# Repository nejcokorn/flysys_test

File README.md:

# FlySys Hardware Plan

Updated: 2026-06-08

This folder is intentionally a planning workspace only. The next hardware build will be created from scratch in Atopile. Old EasyEDA, KiCad, generated production files, and JLC-specific draft outputs are not part of the active design.

## Goal

Build a compact FlySys variometer board with:

- BLE-first telemetry and configuration.
- Accurate pressure-based vertical-speed sensing.
- 6-axis inertial sensing for filtering/orientation support.
- LiPo charging and battery operation.
- Loud firmware-controlled audio output.
- USB mass-storage device access for logs/configuration.
- Power button, hidden BOOT/RESET recovery controls, green power LED, blue BLE pairing LED, USB, and software-first firmware update access without debug pads.

## Selected Components

| Function | Selection | Supplier note |
| --- | --- | --- |
| MCU/BLE/Wi-Fi/USBMSD | Espressif `ESP32-S3-WROOM-1U-N8` | Use ESP32-S3 because USBMSD needs configurable USB device support. `N8` provides 8 MB flash and has no PSRAM. The `1U` variant uses the module U.FL/I-PEX MHF1 connector for an off-board antenna. |
| External antenna | Pulse `ANTX200P001B24003` | Off-board 2.4 GHz adhesive flat patch antenna for the WROOM-1U U.FL/I-PEX MHF1 connector. It is a DigiKey order item, not a PCB footprint. |
| Pressure sensors | 2 x Bosch `BMP581` | Dual altitude/variometer pressure sensors on the same I2C bus. `U5` uses address `0x46`; `U6` uses address `0x47`. |
| 6-axis IMU | Bosch `BMI323` | Primary accelerometer/gyro. |
| Magnetometer | Not fitted | Keep unpopulated I2C pads or optional footprint for future magnetometer. |
| Charger / power path | TI `BQ24075RGTR` | 1S LiPo charger with power-path management. |
| 3.3 V regulator | TI `TLV75533PDBVR` | Replaces `AP2112K-3.3TRG1` because AP2112 was 0 stock in the DigiKey.si audit. Recheck current and thermal margin with ESP32-S3 peaks. Add local bulk capacitance near the module. |
| USB | GCT `USB4105-GF-A` + ST `USBLC6-2SC6Y` | USB-C 2.0 receptacle and automotive/AEC-Q101 USB ESD for charging, ESP32-S3 native USB, USBMSD, logs, and flashing. |
| Audio | Same Sky `CSS-J4D20-SMT-TR` + `AO3400A` N-MOSFET | Externally driven SMD magnetic transducer from the old device BOM. Drive from the 1S battery/SYS rail; keep firmware tone, carrier-duty, and envelope control. |
| User input | C&K `KMR211NG LFS` | Momentary active-low tactile switch for power/user input plus hidden BOOT and RESET service switches. Final actuator and pinhole geometry still depends on enclosure height. |
| Indicators | Lite-On `LTST-C190GKT` + `LTST-C190TBKT` | 0603 LEDs: green always-on `+3V3` power-present indicator, blue firmware-controlled BLE pairing/advertising indicator. The blue LED is driven from `SYS` with a GPIO-controlled low-side MOSFET. |
| Battery | JST `S2B-PH-SM4-TB` | 2-pin JST-PH right-angle SMD header. Confirm protected pack and cable polarity. |
| Firmware update | Application-level updater + hidden ESP32-S3 BOOT/RESET recovery | Normal users update through firmware while USB or another supported link is connected. Debug pads are not fitted; hidden BOOT+RESET remains the recovery fallback for the ESP32-S3 ROM USB bootloader. |

## DigiKey.si Availability Audit

Initial audit checked: 2026-05-31. Audio and LED changes rechecked: 2026-06-01. Stock changes quickly; recheck before ordering.

| Function | MPN | DigiKey cut-tape part | Observed availability | Status |
| --- | --- | --- | --- | --- |
| MCU/BLE/Wi-Fi/USBMSD | `ESP32-S3-WROOM-1U-N8` | `1965-ESP32-S3-WROOM-1U-N8CT-ND` | Recheck before ordering | Selected external-antenna module |
| External antenna | `ANTX200P001B24003` | `311-1553-ND` | Recheck before ordering | Off-board U.FL/I-PEX MHF1 adhesive 2.4 GHz antenna |
| Pressure sensors | `BMP581` | `828-BMP581CT-ND` | Recheck before ordering | Qty 2 selected |
| 6-axis IMU | `BMI323` | `828-BMI323CT-ND` | 663 in stock | Selected |
| Charger / power path | `BQ24075RGTR` | `296-38874-1-ND` | 3,702 in stock | Selected |
| 3.3 V LDO | `TLV75533PDBVR` | `296-50411-1-ND` | 110,688 in stock | Selected |
| USB-C receptacle | `USB4105-GF-A` | `2073-USB4105-GF-ACT-ND` | 126,702 in stock | Selected |
| USB ESD | `USBLC6-2SC6Y` | `497-11882-1-ND` | 35,783 in stock | Selected automotive/AEC-Q101 part; LCSC `C2969755` |
| Battery connector | `S2B-PH-SM4-TB` | `455-S2B-PH-SM4-TBCT-ND` | 71,350 in stock | Selected |
| Loud SMD buzzer | `CSS-J4D20-SMT-TR` | `102-1198-1-ND` | 2,332 in stock | Selected old-device buzzer: externally driven magnetic transducer, 90 dB at 3.6 V, 5 cm, 80 mA, 3.1 kHz |
| N-MOSFETs | `AO3400A` | `785-1000-1-ND` | 168,023 in stock | Low-side drivers for buzzer PWM, blue BLE pairing LED switching, and power-latch control |
| Battery switch P-MOSFET | `DMP3098L-7` | `DMP3098LDICT-ND` | Recheck before ordering | High-side hard-off switch between battery connector and internal `BAT` rail |
| Power-start diodes | `1N4148W-7-F` | `1N4148W-FDICT-ND` | Recheck before ordering | Diode isolation for power button, battery switch gate, and charger `SYSOFF` |
| User button | `KMR211NG LFS` | `CKN10243CT-ND` | 44,917 in stock | Selected |
| Power LED | `LTST-C190GKT` | `160-LTST-C190GKTCT-ND` | 1,068,260 in stock | Selected 0603 green LED, 2.1 V typical Vf |
| BLE LED | `LTST-C190TBKT` | `160-1646-1-ND` | 92,246 in stock | Selected 0603 blue LED for BLE pairing/advertising indication, 3.3 V typical Vf |
| Resistors | Yageo `RC0603FR` 1% 0603 family | Value-specific | `RC0603FR-0710KL` observed at 9,468,329 in stock | Use same family for 100R, 1k, 3k, 5.1k, 10k, 100k, 1M as needed |
| 100 nF decoupling capacitor | Samsung `CL10B104KB8NNNC` | `1276-1000-1-ND` | 9,953,497 in stock | Selected family |
| Other ceramics | Samsung CL-series MLCCs | Value-specific | Not individually locked yet | Select exact 1 uF, 10 uF, and 220 nF parts during Atopile binding |

Main audit result: all selected active semiconductors, sensors, connector choices, audio parts, button, LED, and common passives are available from DigiKey.si.

## Baseline Electrical Architecture

- `USB_VBUS`: USB-C 5 V input to charger and USB VBUS sense divider/comparator.
- `SYS`: BQ24075 system output.
- `BAT_RAW`: protected 1S LiPo positive terminal at the connector.
- `BAT`: switched internal battery rail after the hard-off P-MOSFET.
- `+3V3`: TLV75533 output powering ESP32-S3, both BMP581 sensors, BMI323, and optional magnetometer pads.
- `I2C_SCL`, `I2C_SDA`: shared sensor bus for BMP581 `U5`, BMP581 `U6`, BMI323, and DNP magnetometer option.
- `USB_OTG_DP`, `USB_OTG_DM`: USB full-speed pair to ESP32-S3 native USB pins (`GPIO20` D+, `GPIO19` D-).
- `BUZZER_VM`: battery/SYS-powered audio rail feeding the buzzer; no boost in the baseline.
- `BUZZER_PWM`: ESP32-S3 PWM-capable GPIO to the MOSFET gate.
- `PWR_SW_N`: raw active-low power switch node.
- `PWR_BTN_N`: diode-isolated active-low button input to ESP32-S3.
- `BOOT_USER_BTN_N`: ESP32-S3 GPIO0 boot strap, pulled low by the hidden BOOT service button for ROM bootloader recovery.
- `BAT_SENSE`: high-value divider from switched `BAT` to ESP32-S3 ADC-capable GPIO; it has no DC path to `BAT_RAW` when the hard-off switch is open.
- `POWER_LED`: low-current green `+3V3` rail indicator with series resistor. It is on whenever `+3V3` is up and is not firmware-controlled.
- `BLE_LED`: low-current blue indicator for BLE pairing/advertising mode only. Firmware should drive `BLE_LED_PWM` active only while connectable BLE advertising/pairing is active and keep it low or high-Z otherwise. Because the blue LED has high forward voltage, prefer `SYS` plus a current-limit resistor and a small GPIO-controlled low-side switch instead of direct `+3V3` GPIO drive.
- `EN`, `BOOT`: hidden physical RESET and BOOT service controls for ESP32-S3 ROM bootloader recovery only.

## USBMSD / Storage Plan

USBMSD is now a baseline requirement. Use ESP32-S3 native USB OTG device mode with the ESP-IDF TinyUSB MSC class.

Route the USB-C D+/D- pair to ESP32-S3 `GPIO20`/`GPIO19`, keep the ESD part near the connector, and add a USB VBUS monitor path because this is a battery-powered, self-powered USB device.

Initial storage options:

- Internal flash FAT partition for small configuration import/export and short log files.
- External SPI flash, SPI NAND, or microSD if host-visible logs need materially more capacity or write endurance.

Do not let firmware and the USB host write the same mounted filesystem at the same time. Define a mode switch or mount arbitration before implementing firmware.

## Firmware Update UX

Normal firmware update is software-first. When USB is connected, application
firmware should expose an update path such as USB MSC drag-and-drop firmware
copy, a USB CDC update tool, BLE DFU, or OTA. The image must be validated before
activation, and firmware should use OTA partitions with rollback so a failed
image can revert automatically.

USB attach is allowed to power the ESP32-S3 electrically. If `USB_VBUS_SENSE`
shows USB present and the user has not pressed `POWER`, firmware enters
USB-attached idle mode instead of starting the vario application. In this mode,
do not start vario sensing, BLE advertising, buzzer output, logging, or normal
flight behavior. Only minimal charging/status indication, the firmware update
endpoint, and an optional command to start normal mode should run.

Pressing `POWER` while USB is connected records user intent and starts the normal
application. The hidden `BOOT` (`GPIO0`) and `RST` (`EN`) controls remain behind
service access only. Recovery sequence: connect USB-C, hold hidden `BOOT`, press
and release hidden `RST`, release `BOOT`, then flash with the ESP32-S3 native USB
ROM bootloader tool.

## Audio Plan

The buzzer must be loud enough for a paragliding vario used in open air with wind noise. Treat acoustic output as a primary requirement, not a secondary indicator.

Use an externally driven passive SMD transducer so firmware keeps control over pitch, cadence, envelope, mute profiles, and sink/climb tone patterns. Do not use an internally driven active buzzer.

Selected audio path:

- Transducer: `CSS-J4D20-SMT-TR`, externally driven magnetic SMD transducer from the old device BOM, 90 dB at 3.6 V, 5 cm, 3.1 kHz, about 80 mA at rated drive.
- Driver: `AO3400A` low-side N-MOSFET, with the buzzer powered from the 1S battery/SYS rail and the MOSFET gate driven by one ESP32-S3 PWM GPIO.

This matches the old `MX270_MiniUP` firmware model: one output-compare PWM channel generated the audio carrier, `beep->volume` changed the carrier duty, and the vario queue changed the beep envelope/cadence. Port that control model to ESP32-S3 LEDC or MCPWM.

Use the battery/SYS rail, not raw USB VBUS. A normal 1S Li-ion/LiPo pack is 4.2 V full and about 3.6-3.7 V nominal; that fits the buzzer's 3-5 V operating range. Confirm BQ24075 `SYS` behavior so the buzzer never sees an out-of-range USB-derived rail.

Drive the buzzer near its 3.1 kHz rated frequency for maximum SPL. For lower volume, prefer carrier-duty control and audible envelope control; avoid detuning far from resonance just to reduce volume. The old firmware's tone table can be reused as a behavioral reference, but final tones should be revalidated against this buzzer in the enclosure.

Add a gate resistor, gate pulldown, local bulk capacitance near the buzzer supply, and a footprint option for coil clamp/snubber parts. Keep the buzzer current loop compact and scope the first PCB for ringing and EMI while the buzzer is running.

The enclosure must include a real acoustic outlet or sound channel. Verify SPL after the PCB is installed in the actual enclosure, because the port, chamber volume, venting, clothing, helmet, and mounting orientation can dominate the result.

## Sensor Plan

Use two BMP581 barometers and one BMI323 as the fitted sensor stack.

`U5` straps `SDO` to `GND` for BMP581 I2C address `0x46`; `U6` straps `SDO` to `+3V3` for address `0x47`. Both sensors strap `CSB` high for I2C mode and have separate interrupt nets, `BMP581_1_INT` and `BMP581_2_INT`.

Do not fit a magnetometer for the first Atopile board. The core variometer behavior depends on pressure and vertical-motion filtering, not absolute compass heading. Without a magnetometer, yaw/heading can drift; that is acceptable for this baseline.

Keep an unpopulated future magnetometer option with:

- `+3V3`
- `GND`
- `I2C_SCL`
- `I2C_SDA`
- Optional `MAG_INT`

Place the optional magnetometer pads away from USB shield, charger, buzzer, battery current loops, steel screws, and magnets.

## Layout Constraints

- Put the ESP32-S3-WROOM-1U-N8 so its U.FL/I-PEX MHF1 connector is accessible for the off-board antenna cable. Provide coax strain relief and keep the antenna away from battery metal, buzzer metal, enclosure metal, and the user's body as much as the enclosure allows.
- Put both BMP581 sensors near the pressure vent and away from heat, board flex, adhesive, conformal coating, and direct buzzer airflow.
- Put BMI323 near the board center in a mechanically stable area and document axis orientation.
- Keep sensor supply decoupling close to each VDD/VDDIO pin.
- Keep USB D+/D- short, impedance-conscious, protected by ESD near the connector, and routed to ESP32-S3 `GPIO20`/`GPIO19`.
- Include USB VBUS monitoring suitable for self-powered USB device behavior.
- Give the buzzer a clear acoustic outlet; do not bury the port in a sealed or foam-covered enclosure pocket.
- Keep buzzer switching current and charger return currents away from sensor ground return.
- Avoid assigning functional loads to ESP32-S3 boot strapping pins, USB pins, and flash/PSRAM-reserved pins until boot behavior and the exact module variant are checked.

## Firmware Impact

- Port board support from Arduino Nano 33 BLE Sense Rev2 / nRF52840 assumptions to ESP32-S3.
- Use ESP32-S3 BLE stack and keep transmission duty cycle low in production.
- Add USBMSD using ESP-IDF TinyUSB MSC over ESP32-S3 native USB OTG.
- Define the USBMSD storage backend and host-visible filesystem.
- Prevent concurrent writes between firmware logging/config code and the mounted USB host filesystem.
- Decide whether USB presents MSC only, CDC+MSC composite, or a boot/mode-selected function.
- Add software-first firmware update handling with image validation and OTA partition rollback.
- On USB attach from off state, enter USB-attached idle mode until `PWR_BTN_N` is pressed or a supported start command is received.
- In USB-attached idle mode, keep vario sensing, BLE normal operation, buzzer output, and logging inactive.
- Add direct dual-BMP581 driver support for I2C addresses `0x46` and `0x47`, including separate `BMP581_1_INT` and `BMP581_2_INT` handling.
- Add direct BMI323 driver support.
- Remove required magnetometer reads from the baseline firmware path.
- Rework GPIO mapping for ESP32-S3, including `BUZZER_PWM`, `PWR_BTN_N`, `PWR_HOLD`, `BAT_SENSE`, `BLE_LED_PWM`, I2C, USB, `EN`, and `BOOT`.
- Add configurable audio profiles for vario use: climb cadence, sink alarm, mute, startup check, and volume/power-saving modes.
- Port the old single-PWM buzzer model, then retune frequency and volume tables around the `CSS-J4D20-SMT-TR` response on the new PCB.
- Revalidate sensor axis mapping and calibration on the actual PCB.

## Open Decisions

- Protected LiPo pack and cable polarity.
- USBMSD storage backend: internal flash FAT partition vs external flash/NAND/microSD.
- USB device mode policy: MSC only, CDC+MSC composite, boot/mode-selected function, and the exact software update endpoint.
- Final volume-control policy: envelope levels, quiet mode, and startup volume.
- Enclosure acoustic outlet, port orientation, and measured SPL after installation.
- Button actuator/enclosure mechanics.
- Final ESP32-S3 GPIO map after strapping-pin, USB-pin, and reserved-pin review.
- Whether `ESP32-S3-WROOM-1U-N8` without PSRAM is sufficient for the final USBMSD firmware.
- RF/EMC certification path for the selected 4.4 dBi external antenna. Espressif's module certification guidance recommends antennas no higher than the certified antenna gain, so this antenna choice may require additional testing.
- TLV75533 current and thermal margin with ESP32-S3 RF peaks and USB-attached operation.
- Whether charger status pins need LEDs or only test pads.
- Final Atopile package/footprint sources and exact passive values.

## Atopile Build Order

1. Create Atopile project scaffold.
2. Add verified packages for ESP32-S3-WROOM-1U-N8, two BMP581 sensors, BMI323, BQ24075, TLV75533, USB-C, USB ESD, LiPo connector, CSS-J4D20 buzzer, MOSFET driver, button, green power LED, blue BLE pairing LED, passives, and the BOM-only external antenna.
3. Capture power path and 3.3 V rail.
4. Capture ESP32-S3 native USB OTG, USB VBUS sense, `EN`, `BOOT`, and hidden service bootloader buttons.
5. Capture both BMP581 sensors and BMI323 on shared I2C.
6. Add unpopulated magnetometer I2C pads or optional footprint.
7. Add the selected USBMSD storage backend if external storage is selected.
8. Capture loud audio and user I/O.
9. Assign supplier/manufacturer metadata for audit.
10. Run electrical/package checks before PCB routing.

## Atopile Project Status

Atopile is now the active project source in this repo:

- `ato.yaml`: Atopile 0.15.7 project config.
- `main.ato`: FlySysVario schematic source and Atopile `RectangularBoardShape` board outline.
- `parts/`: generated and local part definitions, including local draft footprints for battery, buzzer, MOSFETs, signal diodes, buttons, and optional magnetometer pads.
- `layouts/default/default.kicad_pcb`: Atopile-generated layout artifact used by the Atopile Autolayout panel.
- `docs/components-and-placement.md`: component map, passive explanations, and placement intent.

Current modeled nets include USB-C, USB ESD, BQ24075 power path, P-MOS battery hard-off switch, TLV75533 3.3 V rail, ESP32-S3 native USB, I2C sensor bus, two BMP581 barometers, BMI323, battery connector, switched battery/USB sense dividers, buzzer MOSFET driver, always-on green power LED, blue BLE pairing LED low-side switch, power/user button, hidden BOOT and RESET service buttons, and optional future magnetometer pads. See `docs/firmware-update-ux.md` for the software-first update flow and recovery fallback.

`ato --non-interactive build --standalone main.ato:FlySysVario` completes the
current Atopile source workflow. The default layout build still needs a layout
artifact migration after the WROOM-1U swap; `ato --non-interactive build`
passes electrical verification but fails while loading `layouts/default/default.kicad_pcb`.
The 90 mm x 45 mm board outline is defined in `main.ato` with
`RectangularBoardShape`, so the Atopile Autolayout panel has a board boundary to
place and route against. The remaining warnings are expected for local or
DigiKey-only parts because the current picker support is not covering those
local packages. Before production, verify the local draft footprints for
`ESP32-S3-WROOM-1U-N8`, `S2B-PH-SM4-TB`, `CSS-J4D20-SMT-TR`, `AO3400A`,
`DMP3098L`, `1N4148W`, `KMR211NG LFS`, and optional magnetometer pads against
manufacturer land patterns and enclosure mechanics.

## Source Links

- Atopile project structure: https://docs.atopile.io/atopile-0.14.x/essentials/5-project-structure
- Atopile language reference: https://docs.atopile.io/atopile-0.14.x/essentials/1-the-ato-language
- ESP32-S3-WROOM-1/WROOM-1U datasheet: https://documentation.espressif.com/esp32-s3-wroom-1_wroom-1u_datasheet_en.pdf
- DigiKey.si ESP32-S3-WROOM-1U-N8: https://www.digikey.si/en/products/detail/espressif-systems/ESP32-S3-WROOM-1U-N8/16162635
- DigiKey.si Pulse ANTX200P001B24003: https://www.digikey.si/en/products/detail/pulse-electronics/ANTX200P001B24003/3927174
- ESP-IDF ESP32-S3 USB Device Stack / TinyUSB MSC: https://docs.espressif.com/projects/esp-usb/en/latest/esp32s3/usb_device.html
- ESP-IDF ESP32-C3 USB Serial/JTAG fixed-function note: https://docs.espressif.com/projects/esp-idf/en/release-v5.2/esp32c3/api-guides/usb-serial-jtag-console.html
- Bosch BMP581: https://www.bosch-sensortec.com/en/products/environmental-sensors/pressure-sensors/bmp581/
- Bosch BMP581 datasheet / land pattern: https://www.bosch-sensortec.com/media/boschsensortec/downloads/datasheets/bst-bmp581-ds004.pdf
- DigiKey.si BMP581: https://www.digikey.si/en/products/detail/bosch-sensortec/BMP581/16036134
- Bosch BMI323: https://www.bosch-sensortec.com/en/products/motion-sensors/imus/bmi323/
- DigiKey.si BMI323: https://www.digikey.si/en/products/detail/bosch-sensortec/BMI323/16719593
- TI BQ24075: https://www.ti.com/product/BQ24075
- DigiKey.si BQ24075RGTR: https://www.digikey.si/en/products/detail/texas-instruments/BQ24075RGTR/2047273
- DigiKey.si TLV75533PDBVR: https://www.digikey.si/en/products/detail/texas-instruments/TLV75533PDBVR/9356541
- DigiKey.si USB4105-GF-A: https://www.digikey.si/en/products/detail/gct/USB4105-GF-A/11198441
- DigiKey.si USBLC6-2SC6Y: https://www.digikey.si/en/products/detail/stmicroelectronics/USBLC6-2SC6Y/2819177
- DigiKey.si S2B-PH-SM4-TB: https://www.digikey.si/en/products/filter/headers-male-pins/314?s=N4Ig7CBcoIYE5QIwA5EGYA0IYBcmZAAcBLJAJjLUQE4wBfOoA
- DigiKey.si CSS-J4D20-SMT-TR: https://www.digikey.si/en/products/detail/same-sky-formerly-cui-devices/CSS-J4D20-SMT-TR/504819
- DigiKey.si AO3400A: https://www.digikey.si/en/products/detail/alpha-omega-semiconductor-inc/AO3400A/1855772
- DigiKey.si KMR211NG LFS: https://www.digikey.si/en/products/detail/c-k/Y78B21120FP/2176482
- DigiKey.si LTST-C190GKT: https://www.digikey.si/en/products/detail/lite-on-inc/LTST-C190GKT/269230
- DigiKey.si LTST-C190TBKT: https://www.digikey.si/en/products/detail/lite-on-inc/LTST-C190TBKT/388529
- DigiKey.si RC0603FR resistor family: https://www.digikey.si/en/products/filter/chip-resistor-surface-mount/52
- DigiKey.si CL10B104KB8NNNC: https://www.digikey.si/en/products/detail/samsung-electro-mechanics/CL10B104KB8NNNC/3886658

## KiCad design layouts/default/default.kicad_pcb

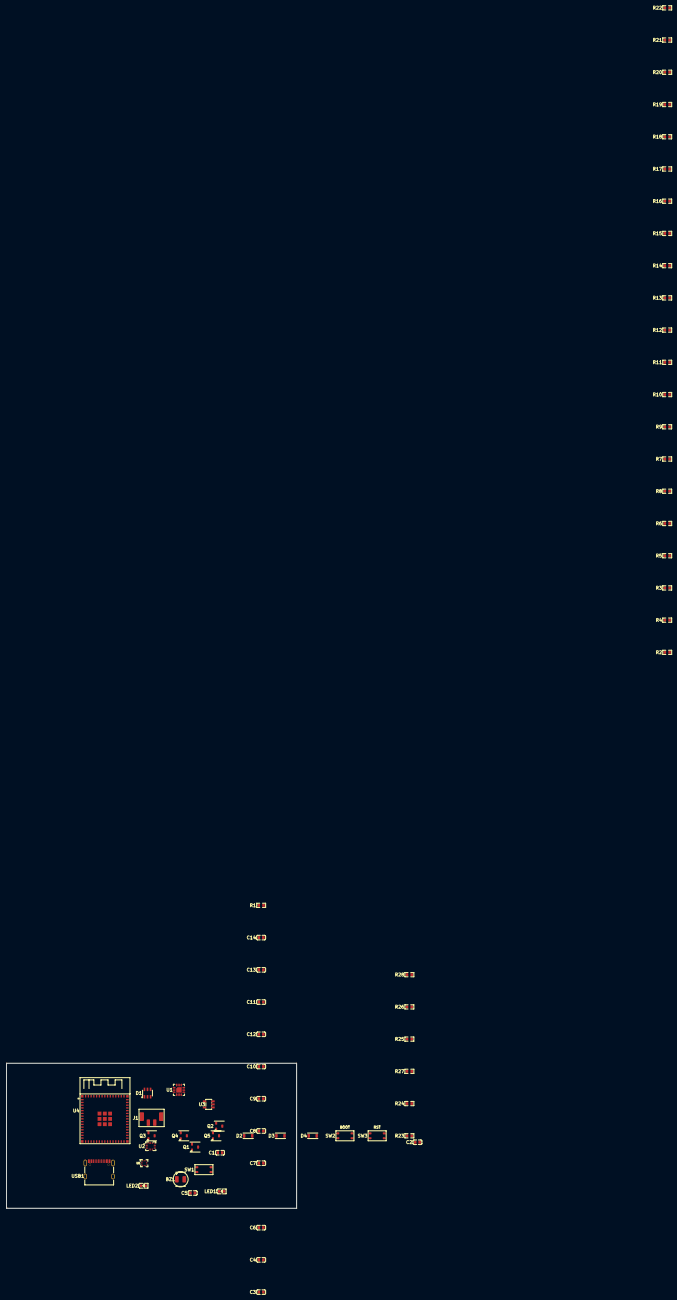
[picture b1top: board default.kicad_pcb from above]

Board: 2 copper layers, 90.0 x 45.0 mm, 64 parts (0 on the bottom side), 41 nets, no tracks yet.

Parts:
BZ1: CSS-J4D20-SMT-TR
C1, C3, C9, C13: 10µF ±10%; C0603
C2, C4, C5, C6, C10, C11, C12: 100nF ±10%; C0603
C7, C8, C14: 1µF ±10%; C0603
D1: SOT-23-6_L2.9-W1.6-P0.95-LS2.8-BL
D2, D3, D4: 1N4148W
J1: S2B-PH-SM4-TB
LED1, LED2: LED0603-RD
Q1, Q2, Q3, Q5: AO3400A
Q4: DMP3098L
R1, R2, R22, R23, R25, R28: 1MΩ ±1%; R0603
R3, R7, R26: 100kΩ ±1%; R0603
R4, R8, R27: 100Ω ±1%; R0603
R5, R20: 1kΩ ±1%; R0603
R6, R13, R15, R16, R19: 10kΩ ±1%; R0603
R9, R10: 5.1kΩ ±1%; R0603
R11: 1.1kΩ ±1%; R0603
R12: 2kΩ ±1%; R0603
R14: 47kΩ ±1%; R0603
R17, R18, R24: 4.7kΩ ±1%; R0603
R21: 330kΩ ±1%; R0603
SW1: KMR211NG_LFS
SW2: KMR211NG_LFS_BOOT
SW3: KMR211NG_LFS_RST
U1: QFN-16_L3.0-W3.0-P0.50-TL-EP1.7
U2: LGA-14_L3.0-W2.5-P0.50-TL_QMI8658A
U3: SOT-23-5_L3.0-W1.7-P0.95-LS2.8-BR
U4: BULETM-SMD_ESP32-S3-MINI-1-N8
U5: BMP581_LGA10_2x2mm
USB1: TYPE-C-SMD_SBC-160S1A-20-S412

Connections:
4: U2.4, U4.9
10: U2.9, U4.10
14: R27.1, U4.14
21: R8.1, U4.21
22: R4.1, U4.22
A: LED1.2, R5.2
A5: R9.1, USB1.A5
B5: R10.1, USB1.B5
BAT_SENSE: C2.1, R1.1, R2.2, U4.5
BAT_SWITCH_GATE: D3.2, Q4.1, Q5.3, R23.1
BLE_LED_GATE: Q2.1, R3.1, R4.2
BOOT_USER_BTN_N: R6.1, SW2.1, SW2.2, U4.4
BUZZER_GATE: Q1.1, R7.1, R8.2
CHG_SYSOFF: D4.2, Q3.3, R28.1, U1.15
DRAIN: LED1.1, Q2.3
DRAIN-1: BZ1.2, Q1.3
EN: C4.1, R16.1, SW3.1, SW3.2, U4.45
GND: C1.2, C2.2, C3.2, C4.2, C5.2, C6.2, C7.2, C8.2, C9.2, C10.2, C11.2, C12.2, C13.2, C14.2, D1.2, J1.2, LED2.1, Q1.2, Q2.2, Q3.2, Q5.2, R1.2, R3.2, R7.2, R9.2, R10.2, R11.2, R12.2, R14.2, R15.2, R21.2, R25.2, SW1.3, SW1.4, SW2.3, SW2.4, SW3.3, SW3.4, U1.4, U1.6, U1.8, U1.17, U2.1, U2.6, U2.7, U3.2, U4.1, U4.2, U4.42, U4.43, U4.46, U4.47, U4.48, U4.49, U4.50, U4.51, U4.52, U4.53, U4.54, U4.55, U4.56, U4.57, U4.58, U4.59, U4.60, U4.GND, U5.3, U5.5, U5.8, U5.9, USB1.1, USB1.A1, USB1.A12, USB1.B1, USB1.B12
I2C_SCL: R17.1, U2.13, U4.12, U5.2
I2C_SDA: R18.1, U2.14, U4.13, U5.4
ILIM: R11.1, U1.12
INT: U4.8, U5.7
ISET: R12.1, U1.16
PWR_BTN_N: D2.2, R24.1, U4.11
PWR_HOLD_GATE: Q3.1, Q5.1, R25.1, R26.1, R27.2
PWR_SW_N: D2.1, D3.1, D4.1, SW1.1, SW1.2
TMR: R14.1, U1.14
TS: R15.1, U1.1
USB_DM_CONN: D1.3, USB1.A7, USB1.B7
USB_DP_CONN: D1.1, USB1.A6, USB1.B6
USB_OTG_DM: D1.4, U4.23
USB_OTG_DP: D1.6, U4.24
USB_VBUS_SENSE: R21.1, R22.2, U4.6
bat_raw-hv: J1.1, Q4.2, R23.2
c_pressure_vddio-power-hv: C5.1, C6.1, C8.1, C9.1, C10.1, C11.1, C12.1, R6.2, R13.2, R16.2, R17.2, R18.2, R19.2, R20.1, R24.2, R26.2, U2.5, U2.8, U2.12, U3.5, U4.3, U5.1, U5.6, U5.10
c_sys_bulk-power-hv: BZ1.1, C3.1, C7.1, C13.1, R5.1, U1.5, U1.10, U1.11, U3.1, U3.3
c_vbus_in-power-hv: C14.1, D1.5, R22.1, U1.13, USB1.A4, USB1.A9, USB1.B4, USB1.B9
hv: C1.1, Q4.3, R2.1, R28.2, U1.2, U1.3
nCHG: R13.1, U1.9, U4.33
nPGOOD: R19.1, U1.7, U4.34
pos: LED2.2, R20.2

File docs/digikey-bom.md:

# FlySys DigiKey BOM

Updated: 2026-06-03

All purchased components in the KiCad schematic use DigiKey order lines. Debug pads are not fitted; normal firmware update is software-first, and ESP32-S3 bootloader recovery uses USB plus hidden BOOT and RST service buttons.

| References | Qty | Value | Manufacturer | MPN | DigiKey PN | Description |
| --- | ---: | --- | --- | --- | --- | --- |
| Q1, Q2, Q3, Q5 | 4 | AO3400A | Alpha & Omega Semiconductor Inc. | AO3400A | [785-1000-1-ND](https://www.digikey.com/en/products/detail/alpha-omega-semic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 | N-channel MOSFET, SOT-23 |
| U2 | 1 | BMI323 | Bosch Sensortec | BMI323 | [828-BMI323CT-ND](https://www.digikey.com/en/products/detail/bosch-sensortec/B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 | 6-axis IMU |
| U5 | 1 | BMP581 | Bosch Sensortec | BMP581 | [828-BMP581CT-ND](https://www.digikey.com/en/products/detail/bosch-sensortec/B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 | Barometric pressure sensor |
| SW1, SW2, SW3 | 3 | KMR211NG LFS | C&K | KMR211NG LFS | [CKN10243CT-ND](https://www.digikey.com/en/products/detail/c-k/KMR211NG-LFS/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 | Low-profile tactile switch |
| D2, D3, D4 | 3 | 1N4148W | Diodes Incorporated | 1N4148W-7-F | [1N4148W-FDICT-ND](https://www.digikey.com/en/products/detail/diodes-incorporat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 | Small-signal switching diode, SOD-123 |
| Q4 | 1 | DMP3098L | Diodes Incorporated | DMP3098L-7 | [DMP3098L-7DICT-ND](https://www.digikey.com/en/products/detail/diodes-incorporat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 | P-channel MOSFET, SOT-23 |
| U4 | 1 | ESP32-S3-MINI-1-N8 | Espressif Systems | ESP32-S3-MINI-1-N8 | [5407-ESP32-S3-MINI-1-N8CT-ND](https://www.digikey.com/en/products/detail/espressif-systems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 | ESP32-S3 module with PCB antenna and 8 MB flash |
| USB1 | 1 | USB4105-GF-A | GCT | USB4105-GF-A | [2073-USB4105-GF-ACT-ND](https://www.digikey.com/en/products/detail/gct/USB4105-GF-A/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 | USB-C receptacle, USB 2.0, right angle |
| J1 | 1 | S2B-PH-SM4-TB | JST Sales America Inc. | S2B-PH-SM4-TB | [455-S2B-PH-SM4-TBCT-ND](https://www.digikey.com/en/products/detail/jst-sales-america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 | 2-pin JST PH side-entry SMT header |
| LED2 | 1 | LTST-C190GKT | Lite-On Inc. | LTST-C190GKT | [160-LTST-C190GKTCT-ND](https://www.digikey.com/en/products/detail/lite-on-inc/LTST-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 | Green 0603 LED |
| LED1 | 1 | LTST-C190TBKT | Lite-On Inc. | LTST-C190TBKT | [160-1646-1-ND](https://www.digikey.com/en/products/detail/lite-on-inc/LTST-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 | Blue 0603 LED |
| D1 | 1 | USBLC6-2SC6Y | STMicroelectronics | USBLC6-2SC6Y | [497-11882-1-ND](https://www.digikey.com/en/products/detail/stmicroelectronic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 | Automotive USB ESD protection diode array, SOT-23-6 |
| BZ1 | 1 | CSS-J4D20-SMT-TR | Same Sky (Formerly CUI Devices) | CSS-J4D20-SMT-TR | [102-1198-1-ND](https://www.digikey.com/en/products/detail/same-sky-formerly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 | Externally driven magnetic buzzer |
| C7, C8, C14 | 3 | 1uF | Samsung Electro-Mechanics | CL10A105KB8NNNC | [1276-1860-1-ND](https://www.digikey.com/en/products/detail/samsung-electro-m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 | 1 uF, 50 V, X5R, 0603 capacitor |
| C1, C3, C9, C13 | 4 | 10uF | Samsung Electro-Mechanics | CL10A106KP8NNNC | [1276-1192-1-ND](https://www.digikey.com/en/products/detail/samsung-electro-m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 | 10 uF, 10 V, X5R, 0603 capacitor |
| U1 | 1 | BQ24075RGTR | Texas Instruments | BQ24075RGTR | [296-38874-1-ND](https://www.digikey.com/en/products/detail/texas-instruments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 | Li-ion charger and power-path controller |
| U3 | 1 | TLV75533PDBVR | Texas Instruments | TLV75533PDBVR | [296-50411-1-ND](https://www.digikey.com/en/products/detail/texas-instruments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 | 3.3 V 500 mA LDO regulator |
| C2, C4, C5, C6, C10, C11, C12 | 7 | 100nF | YAGEO | CC0603KRX7R9BB104 | [311-1344-1-ND](https://www.digikey.com/en/products/detail/yageo/CC0603KRX7R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 | 100 nF, 50 V, X7R, 0603 capacitor |
| R3, R7, R24 | 3 | 100k | YAGEO | RC0603FR-07100KL | [311-100KHRCT-ND](https://www.digikey.com/en/products/detail/yageo/RC0603FR-07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 | 100 kohm, 1%, 0.1 W, 0603 resistor |
| R4, R8, R25 | 3 | 100R | YAGEO | RC0603FR-07100RL | [311-100HRCT-ND](https://www.digikey.com/en/products/detail/yageo/RC0603FR-07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 | 100 ohm, 1%, 0.1 W, 0603 resistor |
| R6, R13, R15, R16, R19 | 5 | 10k | YAGEO | RC0603FR-0710KL | [311-10.0KHRCT-ND](https://www.digikey.com/en/products/detail/yageo/RC0603FR-07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 | 10 kohm, 1%, 0.1 W, 0603 resistor |
| R11 | 1 | 1.1k | YAGEO | RC0603FR-071K1L | [311-1.10KHRCT-ND](https://www.digikey.com/en/products/detail/yageo/RC0603FR-07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 | 1.1 kohm, 1%, 0.1 W, 0603 resistor |
| R5, R20 | 2 | 1k | YAGEO | RC0603FR-071KL | [311-1.00KHRCT-ND](https://www.digikey.com/en/products/detail/yageo/RC0603FR-07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 | 1 kohm, 1%, 0.1 W, 0603 resistor |
| R1, R2, R22, R23, R26, R28 | 6 | 1M | YAGEO | RC0603FR-071ML | [311-1.00MHRCT-ND](https://www.digikey.com/en/products/detail/yageo/RC0603FR-07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 | 1 Mohm, 1%, 0.1 W, 0603 resistor |
| R12 | 1 | 2k | YAGEO | RC0603FR-072KL | [311-2.00KHRCT-ND](https://www.digikey.com/en/products/detail/yageo/RC0603FR-07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 | 2 kohm, 1%, 0.1 W, 0603 resistor |
| R21 | 1 | 330k | YAGEO | RC0603FR-07330KL | [311-330KHRCT-ND](https://www.digikey.com/en/products/detail/yageo/RC0603FR-07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 | 330 kohm, 1%, 0.1 W, 0603 resistor |
| R14 | 1 | 47k | YAGEO | RC0603FR-0747KL | [311-47.0KHRCT-ND](https://www.digikey.com/en/products/detail/yageo/RC0603FR-07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 | 47 kohm, 1%, 0.1 W, 0603 resistor |
| R17, R18, R27 | 3 | 4.7k | YAGEO | RC0603FR-074K7L | [311-4.70KHRCT-ND](https://www.digikey.com/en/products/detail/yageo/RC0603FR-07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 | 4.7 kohm, 1%, 0.1 W, 0603 resistor |
| R9, R10 | 2 | 5.1k | YAGEO | RC0603FR-075K1L | [311-5.10KHRCT-ND](https://www.digikey.com/en/products/detail/yageo/RC0603FR-07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 | 5.1 kohm, 1%, 0.1 W, 0603 resistor |

Note: Atopile 0.15.7 currently supports only LCSC in its built-in `has_part_picked` BOM path. The DigiKey BOM above is therefore generated by this project script and is the procurement source of truth.

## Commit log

2026-05-31 Create hardware planning baseline
2026-05-31 Add DigiKey availability audit
2026-06-01 Update hardware plan for audio and indicators
2026-06-01 Set power and BLE LED colors
2026-06-01 Add Atopile schematic for FlySys hardware
2026-06-01 Add local BMP581 footprint
2026-06-02 Doc, gerber, kicad
2026-06-02 Add hard-off power path and bootloader buttons
2026-06-03 Boot, reset, USB protection
2026-06-03 Led indicator changes
2026-06-03 Point to digikey.si
2026-06-08 Change ESP add antenna
